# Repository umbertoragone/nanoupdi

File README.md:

# NanoUPDI
The smallest USB Type-C Serial UPDI programmer for your projects. **Available for purchase on [Tindie](https://www.tindie.com/products/ragone/nanoupdi/) or [Lectronz](https://lectronz.com/products/nanoupdi)!**

## What is UPDI?
UPDI is a proprietary programming interface developed by [Atmel/Microchip](https://www.microchip.com), similar to the JTAG/SWD interfaces used for ARM microcontrollers. It's the default programming interface for several newer AVR microcontrollers, including models like the ATTINY212, ATTINY412, ATTINY414, etc. It only requires a single pin for programming, so it's more convenient and efficient.

## Features
- **CH340E/CH340X USB to Serial converter**: A compact version of the well-known WCH CH340x series, which doesn't require an external crystal oscillator.
- **Compact Form Factor**: At only 10 x 22 mm (excluding header pins), it is the smallest serial UPDI programmer on the market.
- **VCC Voltage Selector**: Easily switch between 3.3V (3V3) and 5V logic voltages with a simple flick of a switch.
- **USB Type-C**: Compatible with any USB Type-C cable that supports both power and data (USB 2.0 or greater). The reversible USB Type-C connector allows the cable to be plugged in either orientation, maintaining full functionality (data and power).
- **2.54mm Pitch Pin Header**: Designed for right-angle (horizontal) pin headers with a 0.1" (2.54mm) pitch pin headers (breadboard compatible), it also allows for custom wires or connectors to be soldered based on your needs.
- **Status LEDs**: Includes a green LED for power (PWR) and a red LED that blinks during data transfer (TX).
- Inspired by [Stefan Wagner](https://github.com/wagiminator)'s [SerialUPDI Programmer](https://github.com/wagiminator/AVR-Programmer/tree/master/SerialUPDI_Programmer).

## Installation and how to use
No installation required, it is Plug&Play with the majority of operating systems since the CH340x is a commonly used USB-to-serial converter.

### Avrdude
If you use `avrdude` to program your UPDI compatible AVR microcontrollers, you simply need to specify `serialupdi` as the programmer:

```bash
avrdude -c serialupdi -p t414 -P /dev/tty.usbserial-10
```

Make sure to specify the correct serial device: on Linux devices, NanoUPDI might show up as `/dev/ttyUSBX`, while on MacOS it might show as `/dev/tty.usbserial-XX`.

### Arduino IDE
To use NanoUPDI with the Arduino IDE, first install the [megaTinyCore board support package](https://github.com/SpenceKonde/megaTinyCore), then choose **Serial UPDI** as the programmer in the dropdown menu.

### WebUPDI
For a browser-based programming option, you can use [WebUPDI](https://github.com/manuelkasper/webupdi) — a lightweight tool that runs entirely in your browser with Web Serial API support. Simply connect your NanoUPDI, select your target device, and flash firmware without installing any additional software. Works on Chrome, Edge, Opera and other Chromium-based browsers.

## Kicad files
If you want to open and modify the original project in Kicad 8 (>=8.0.6), you can find both the `.kicad_sch` and `.kicad_pcb` files in the `kicad` folder in this repository. I recommend you use the latest Kicad 8 version available for better compatibility.

## Gerber files
If you want to fabricate your own PCBs from a PCB manufacturer of your choice, you can go ahead and download the `Gerber-v2.x.zip` file from the `gerber` folder in this repository. Upload it or send it to the PCB fabrication house and select the following specifications (if not already filled out):
- **Layers**: 2
- **PCB Thickness**: 1.6 mm
- **PCB Color**: any (green is usually cheaper and faster to produce, but black looks nicer)
- **Outer Copper Weight**: 1 oz
- **Via Covering**: Tented
- **Mark on PCB**: Remove Mark (JLCPCB specific, now free of charge)

## BOM and assembly
Included in this repository is the HTML BOM (`ibom.html`) to help you in the assembly/soldering process after you received your PCBs. You can [access the Interactive HTML BOM here](https://bom.nanoupdi.com), without having to download the .html file. Also, here is the list of components you will have to source and solder yourself:

| Reference(s) | Value                   | Footprint                       | LCSC Part #                                                   | Qty |
|--------------|-------------------------|---------------------------------|---------------------------------------------------------------|-----|
| C1, C4, C5   | 100nF 50V 10% X7R       | C_0603_1608Metric               | [C14663](https://www.lcsc.com/product-detail/C14663.html)     | 3   |
| C2, C3       | 10uF 10V 10% X7R        | C_0805_2012Metric               | [C237493](https://www.lcsc.com/product-detail/C237493.html)   | 2   |
| R1, R2       | 5k1 1%                  | R_0402_1005Metric               | [C25905](https://www.lcsc.com/product-detail/C25905.html)     | 2   |
| R3, R6       | 470R 1%                 | R_0402_1005Metric               | [C25117](https://www.lcsc.com/product-detail/C25117.html)     | 2   |
| R4           | 0R 1%                   | R_0603_1608Metric               | [C21189](https://www.lcsc.com/product-detail/C21189.html)     | 1   |
| R5           | 1k 1%                   | R_0402_1005Metric               | [C11702](https://www.lcsc.com/product-detail/C11702.html)     | 1   |
| D1           | 1N4148                  | D_SOD-523                       | [C727112](https://www.lcsc.com/product-detail/C727112.html)   | 1   |
| D2           | EMERALD/GREEN           | LED_0603_1608Metric             | [C965804](https://www.lcsc.com/product-detail/C965804.html)   | 1   |
| D3           | RED                     | LED_0603_1608Metric             | [C965799](https://www.lcsc.com/product-detail/C965799.html)   | 1   |
| U1           | CH340E                  | MSOP-10_3x3mm_P0.5mm            | [C99652](https://www.lcsc.com/product-detail/C99652.html)     | 1   |
| SW1          | MSK12C02                | MSK12C02                        | [C431540](https://www.lcsc.com/product-detail/C431540.html)   | 1   |
| FB1          | 220R @ 100MHz           | L_0805_2012Metric               | [C85840](https://www.lcsc.com/product-detail/C85840.html)     | 1   |
| USB1         | USB_C_Receptacle_USB2.0 | TYPE-C-31-M-12                  | [C2988369](https://www.lcsc.com/product-detail/C2988369.html) | 1   |
| VREG1        | AP2112K-3.3             | SOT-23-5                        | [C51118](https://www.lcsc.com/product-detail/C51118.html)     | 1   |
| J1           | Conn_01x03              | PinHeader_1x03_P2.54mm_Vertical | [C92159](https://www.lcsc.com/product-detail/C92159.html)     | 1   |

## Component substitutions
- **U1**: in case the CH340E is not available, the [CH340X](https://www.lcsc.com/product-detail/C3035748.html) should be a drop in replacement for the [CH340E](https://www.lcsc.com/product-detail/C99652.html): same footprint, same pinout and basically the same function—at least in the scope of this UPDI programmer.
- **FB1**: you can use a 0R 0805 resistor or solder a jumper wire in place to make it work. The ferrite bead is there to reduce possible noise from the VBUS (5V) line generated by your computer, so it is generally recommended for stability, but not critical. If you leave it empty, the rest of the board will have no power.
- **C1**: it is a decoupling capacitor for VBUS, marked as "do not place", since it is redundant. In fact, on the boards I sell on my [Tindie store]([url](https://www.tindie.com/products/ragone/nanoupdi/)), it is not populated by default.
- **D1**: it can be swapped with a 1k 0402 resistor (loopback resistor between RX and TX). Both solutions will work the same.

## Prebuilt option
If you're looking for a NanoUPDI programmer that's already assembled and ready to go, I offer a prebuilt option that's perfect for those who want a plug-and-play solution without the hassle of sourcing and assembling components. Each unit is handcrafted and fully tested before shipping. **[Check it out on my Tindie store](https://www.tindie.com/products/ragone/nanoupdi/) or on [Lectronz](https://lectronz.com/products/nanoupdi)**.

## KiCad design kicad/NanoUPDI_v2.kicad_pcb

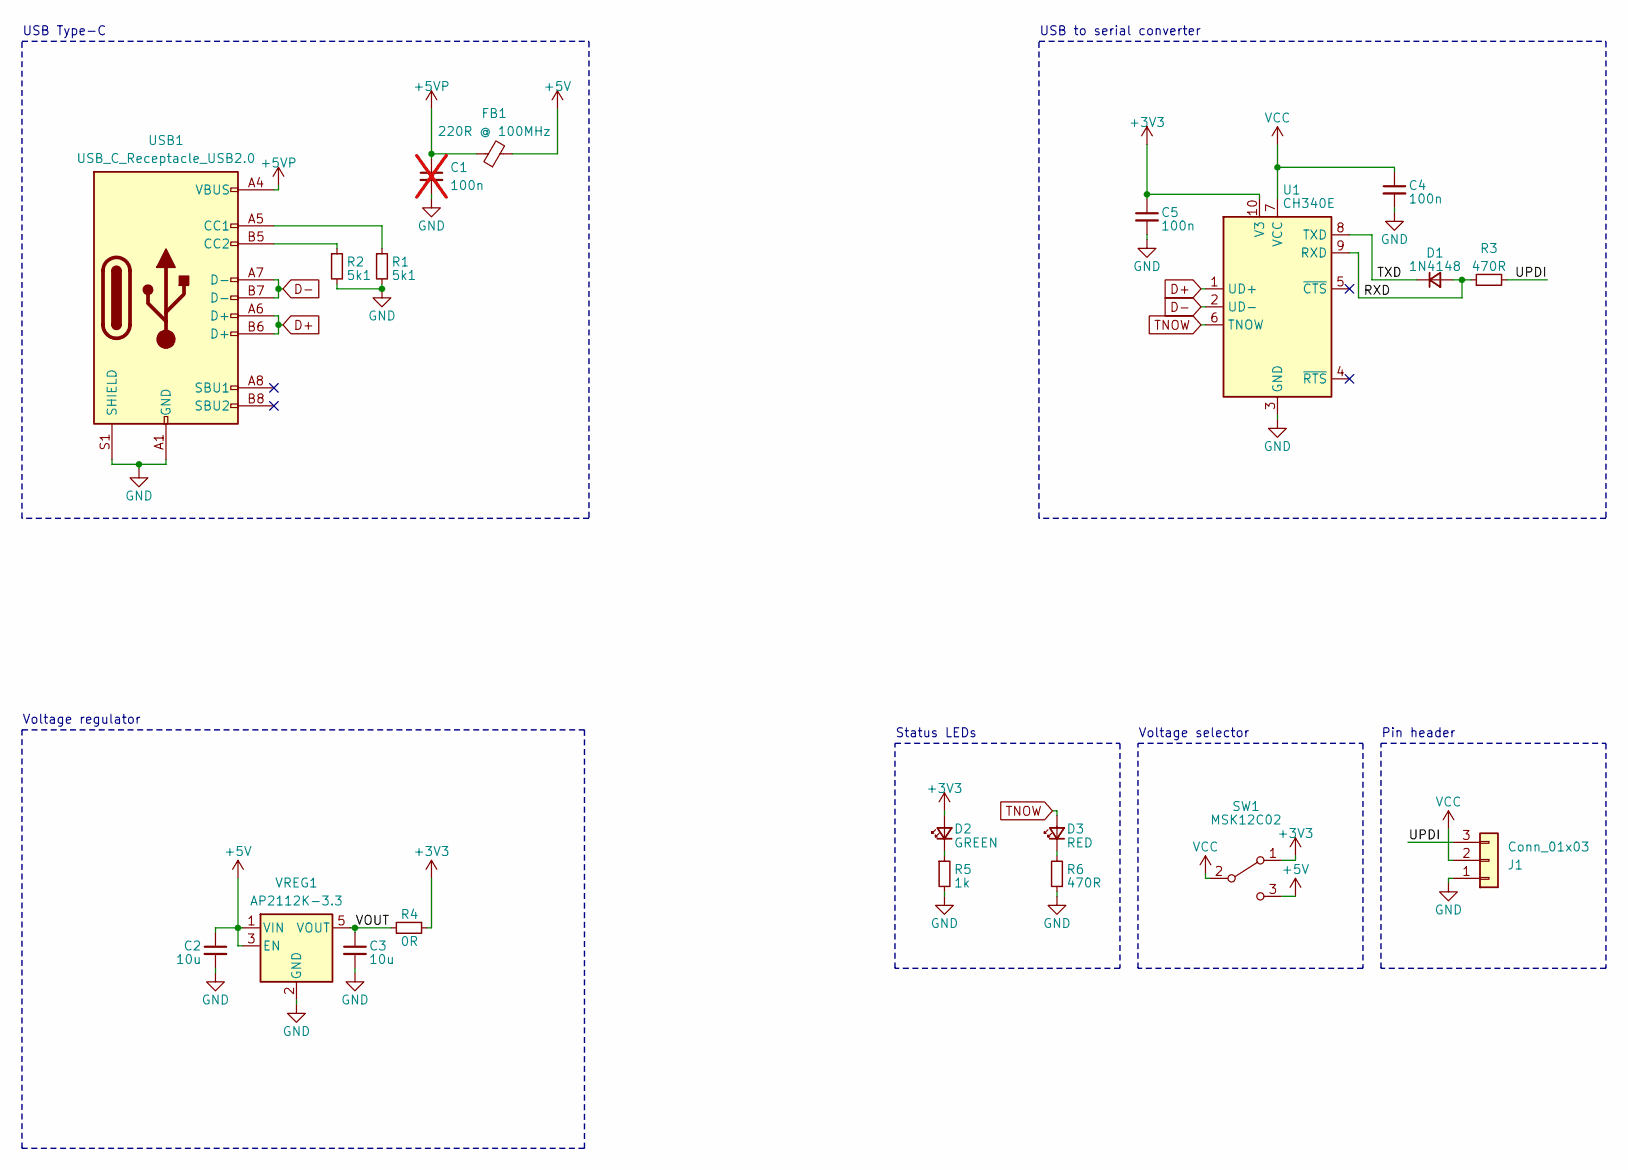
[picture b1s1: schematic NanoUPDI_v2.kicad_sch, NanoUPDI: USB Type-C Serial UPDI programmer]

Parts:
C1: 100n; C_0603_1608Metric; not fitted
C2, C3: 10u; C_0805_2012Metric
C4, C5: 100n; C_0603_1608Metric
D1: 1N4148; D_SOD-523
D2: GREEN; LED_0603_1608Metric
D3: RED; LED_0603_1608Metric
FB1: 220R @ 100MHz; L_0805_2012Metric
J1: Conn_01x03; PinHeader_1x03_P2.54mm_Vertical
R1, R2: 5k1; R_0402_1005Metric
R3, R6: 470R; R_0402_1005Metric
R4: 0R; R_0603_1608Metric
R5: 1k; R_0402_1005Metric
SW1: MSK12C02
U1: CH340E; MSOP-10_3x3mm_P0.5mm
USB1: USB_C_Receptacle_USB2.0; TYPE-C-31-M-12
VREG1: AP2112K-3.3; SOT-23-5

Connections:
+3V3: C5.1, D2.2 (A), R4.1, SW1.1 (A), U1.10 (V3)
+5V: C2.1, FB1.2, SW1.3 (C), VREG1.1 (VIN), VREG1.3 (EN)
+5VP: C1.1, FB1.1, USB1.A4 (VBUS), USB1.A9 (VBUS), USB1.B4 (VBUS), USB1.B9 (VBUS)
/RXD: D1.2 (A), R3.1, U1.9 (RXD)
/TXD: D1.1 (K), U1.8 (TXD)
/UPDI: J1.3, R3.2
/VOUT: C3.1, R4.2, VREG1.5 (VOUT)
D+: U1.1 (UD+), USB1.A6 (D+), USB1.B6 (D+)
D-: U1.2 (UD-), USB1.A7 (D-), USB1.B7 (D-)
GND: C1.2, C2.2, C3.2, C4.2, C5.2, J1.1, R1.2, R2.2, R5.2, R6.1, SW1.MP, U1.3 (GND), USB1.A1 (GND), USB1.A12 (GND), USB1.B1 (GND), USB1.B12 (GND), USB1.S1 (SHIELD), VREG1.2 (GND)
unnamed: D2.1 (K), R5.1
unnamed: D3.1 (K), R6.2
unnamed: R1.1, USB1.A5 (CC1)
unnamed: R2.1, USB1.B5 (CC2)
TNOW: D3.2 (A), U1.6 (TNOW)
VCC: C4.1, J1.2, SW1.2 (B), U1.7 (VCC)

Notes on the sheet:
USB Type-C
Voltage regulator
Voltage selector
USB to serial converter
Pin header
Status LEDs

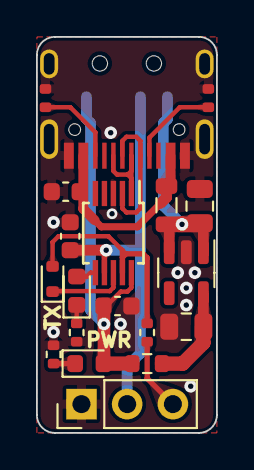
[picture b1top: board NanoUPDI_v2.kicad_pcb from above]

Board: 2 copper layers, 10.0 x 22.0 mm, 20 parts (1 on the bottom side), 16 nets.

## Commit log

2024-11-12 Uploaded renders
2024-11-12 Upload ibom.html
2024-11-12 Upload Gerber.zip
2024-11-12 Upload NanoUPDI images
2024-11-12 Upload up to date Gerber.zip
2024-11-18 Moved to /gerber
2024-11-18 Fix silkscreen for panelization
2024-11-21 Add NanoUPDI schematic
2024-11-21 Add Kicad Schematic
2024-11-21 Add Kicad PCB
2024-11-21 Update Kicad Schematic
2024-11-21 Update Kicad PCB
2024-11-21 Update NanoUPDI schematic
2024-12-13 Add Gerber-v2.2.zip
2024-12-13 Add .gitignore
2024-12-13 Moved R3 further down, fixed MSK12C02 mounting pads, removed "JLCJLCJLCJLC" from silkscreen, updated to v2.2 & date
2024-12-13 Updated solder mask configuration and gerber files for better JLCPCB compatibility
2024-12-13 Fix solder mask expansion
2024-12-14 Remove JLCJLCJLCJLC, tidy up Fab layer
2024-12-14 Removed JLCJLCJLCJLC & minor fixes
2024-12-14 Add ibom preview
2024-12-19 Add link to Interactive HTML BOM to README.md
2026-02-14 Upload new images
2026-04-23 Add WebUPDI section to README.md
    Added information about WebUPDI for browser-based programming.
2026-04-24 Add Opera to supported browsers for WebUPDI
    Updated browser compatibility information for WebUPDI.
